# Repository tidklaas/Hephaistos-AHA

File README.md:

# Hephaistos-AHA
Control your heater from your FritzBox, if you dare...

This project emulates a room thermostat for a central heating unit.
It monitors a set of AVM FritzDect 301 (intelligent radiator valves)
and signals the heater to turn on or off via a simple relay circuit.

Since we are dealing with mains voltage and probably gas-powered
heating systems, you should not even think about using this contraption
unless your are a licensed electrician and/or certified HVAC technician.

Seriously, don't.

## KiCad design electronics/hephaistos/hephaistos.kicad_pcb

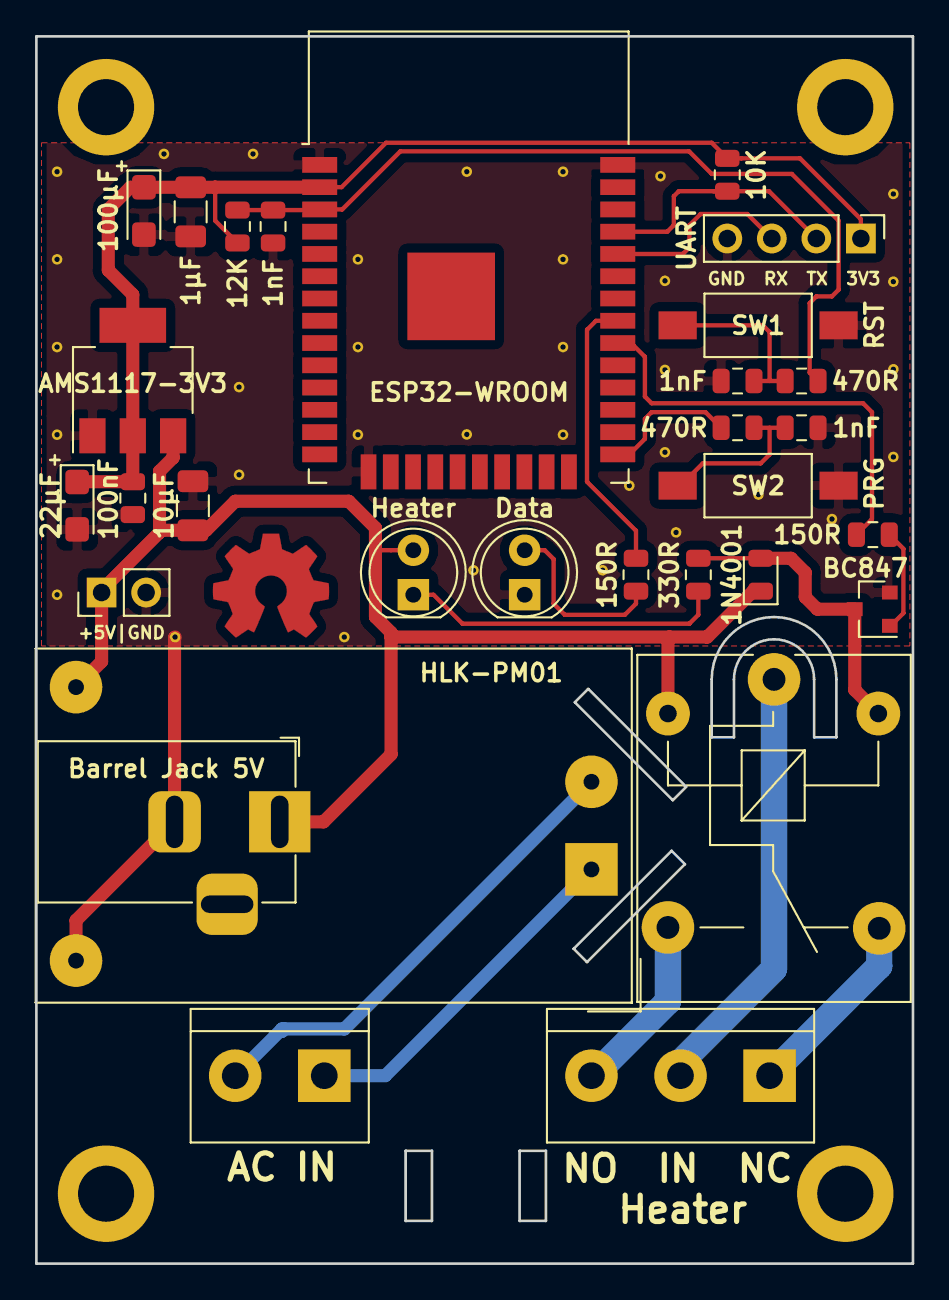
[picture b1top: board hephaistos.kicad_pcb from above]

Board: 2 copper layers, 50.0 x 70.0 mm, 30 parts (0 on the bottom side), 20 nets.

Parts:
C1: 100µF; CP_EIA-3216-12_Kemet-S
C2: 1µF; C_1206_3216Metric
C3, C4, C5: 1nF; C_0805_2012Metric
C6: 10µF; C_1206_3216Metric
C7: 22µF; CP_EIA-3216-12_Kemet-S
C8: 100nF; C_0805_2012Metric
D1: Heater; LED_D5.0mm
D2: Data; LED_D5.0mm
D3: 1N4001; D_0805_2012Metric
J1: UART; PinHeader_1x04_P2.54mm_Vertical
J2: Heater; TerminalBlock_bornier-3_P5.08mm
J3: AC IN; TerminalBlock_bornier-2_P5.08mm
J4: Barrel Jack 5V; BarrelJack_Horizontal
J5: +5V Pin Header; PinHeader_1x02_P2.54mm_Vertical
K1: SANYOU_SRD_Form_C; Relay_SPDT_SANYOU_SRD_Series_Form_C
Q1: BC847; SOT-23
R1: 12K; R_0805_2012Metric
R2, R3: 470R; R_0805_2012Metric
R4: 330R; R_0805_2012Metric
R5, R7: 150R; R_0805_2012Metric
R6: 10K; R_0805_2012Metric
SW1: EN; SW_SPST_FSMSM
SW2: BOOT; SW_SPST_FSMSM
U1: ESP32-WROOM; ESP32-WROOM-32
U2: AMS1117-3V3; SOT-223-3_TabPin2
U3: HLK-PM01; Converter_ACDC_Hi-Link_HLK-PMXX_THT

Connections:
+3V3: C1.1, C2.1, C7.1, C8.1, J1.1, R1.1, R6.2, U1.2, U2.2
+5V: C6.1, D1.2, D3.1, J4.1, J5.1, K1.2, U2.3, U3.4
/IO0: R3.1, U1.25
/IO18: R5.2, U1.30
/IO19: R7.2, U1.31
/REL_IN: J2.2, K1.1
/REL_NC: J2.1, K1.4
/REL_NO: J2.3, K1.3
/RX0: J1.3, U1.34
/TX0: J1.2, R6.1, U1.35
GND: C1.2, C2.2, C3.2, C4.2, C5.2, C6.2, C7.2, C8.2, D2.1, J1.4, J4.2, J5.2, Q1.2, SW1.1, SW2.1, U1.1, U1.15, U1.38, U2.1, U3.3
unnamed: C3.1, R1.2, R2.1, U1.3
unnamed: C4.1, R2.2, SW1.2
unnamed: C5.1, R3.2, SW2.2
unnamed: D1.1, R4.2
unnamed: D2.2, R7.1
unnamed: D3.2, K1.5, Q1.3, R4.1
unnamed: J3.1, U3.1
unnamed: J3.2, U3.2
unnamed: Q1.1, R5.1

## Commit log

2017-11-20 Initial Commit
    - base copied from standard esp-idf examples
    - add expat-dom as submodule component
    - add Kconfig for project configuration (credentials, timezone, ...)
    - add initial implementation of retrieving and parsing AHA data from F!Box
    - add control of heater via GPIO
    - add support for building stand-alone application on UN*X machines
2018-05-24 Enable Task Watchdog and Fix Device Evaluation
    Kconfig:
    - rename CTRL_GPIO to GPIO_HEAT, add GPIO_LED
    hephaistos_aha_main.c:
    - add update indication LED GPIO
    - enable task watchdog
    - ignore group temperature data for heater control
2018-06-14 Refactor AHA Functionality into Separate Task
    - move AHA task into file avm_aha.c
    - add interface for setting and retrieving AHA configuration
    - add interface for access to reference counted AHA data sets
    - add interface for suspend/resume of AHA operation
    - remove support for building stand-alone UNIX binaries
    - remove support for using fake test data from file
2018-06-28 WIP: HTTP Server Running
    - add suspend to AHA task
    - add support for setting/getting WiFi config
    - improve control logic of hephaistos main task
    - add basic configuration via http server
2018-07-25 WIP: Setup/Config/Data via HTTP, Factory Reset
    - add rudimentary support for setting up and reconfiguring device via HTTP
    - add CGI for dumping current AHA data
    - add factory reset functionality via long button press
    - fix serious memory leak in avm_aha when socket read fails
    - remove direct GPIO manipulations from avm_aha, use functions provided
    by main hephaistos module instead.
2018-11-18 WIP: add wifi manager component
2019-05-07 WIP: Dunno...
2019-05-07 WIP: Update to current libesphttpd
    - update libesphttpd submodule
    - add espfs component refactored from libesphttd
    - make necessary changes to httpd_srv.c due to refactoring
2019-06-29 Change libesphttpd and wifi_manager Submodules
    - Move wifi_manager into submodule
    - Change libesphttps' remote URL to https://github.com/tidklaas/libesphttpd.git
2019-09-16 Update wifi_manager
2019-09-16 avm_aha.c: Reduce Console Output
2019-09-16 avm_aha: Fix HKR Parser
    - Data fields for battery may not be present, so check for existence before
    parsing.
    - Add parsing for battery level, open window detection, summer and vacation
    modes.
2019-09-16 Use WiFi Manager
2019-09-23 Integrate phatpaul's wifi cgi improvements
2019-10-06 Update wifi_manager and libesphttpd
2019-10-06 General Clean-Up
    avm_aha:
    - Add heater state (on/off) to aha_data.
    - Let AHA task update its config even when it is suspended. Needed to be
    able to set new AHA config when current config is bogus and system can
    not fetch NTP data.
    heph_cgi:
2019-10-06 Add Hephaistos Hardware
2019-10-06 Fix Link to GitHub Repo on Index Page
2019-10-06 Add License

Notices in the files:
electronics/hephaistos/hephaistos.kicad_pcb:
©2018 Tido Klaassen
